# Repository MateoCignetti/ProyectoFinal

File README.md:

## Repositorio para el proyecto final de la carrera Ingeniería Electrónica. UTN FR San Francisco, 2025.

# Autores
- [ ] Alesandria, Alejo
- [ ] Cignetti, Mateo Antonio
- [ ] Galliano, Ignacio

Shield: [![CC BY-NC-SA 4.0][cc-by-nc-sa-shield]][cc-by-nc-sa]

Esta obra está bajo una
[Licencia Creative Commons Atribución-NoComercial-CompartirIgual 4.0 Internacional][cc-by-nc-sa].

[![CC BY-NC-SA 4.0][cc-by-nc-sa-image]][cc-by-nc-sa]

[cc-by-nc-sa]: https://creativecommons.org/licenses/by-nc-sa/4.0/deed.es
[cc-by-nc-sa-image]: https://licensebuttons.net/l/by-nc-sa/4.0/88x31.png
[cc-by-nc-sa-shield]: https://img.shields.io/badge/License-CC%20BY--NC--SA%204.0-lightgrey.svg

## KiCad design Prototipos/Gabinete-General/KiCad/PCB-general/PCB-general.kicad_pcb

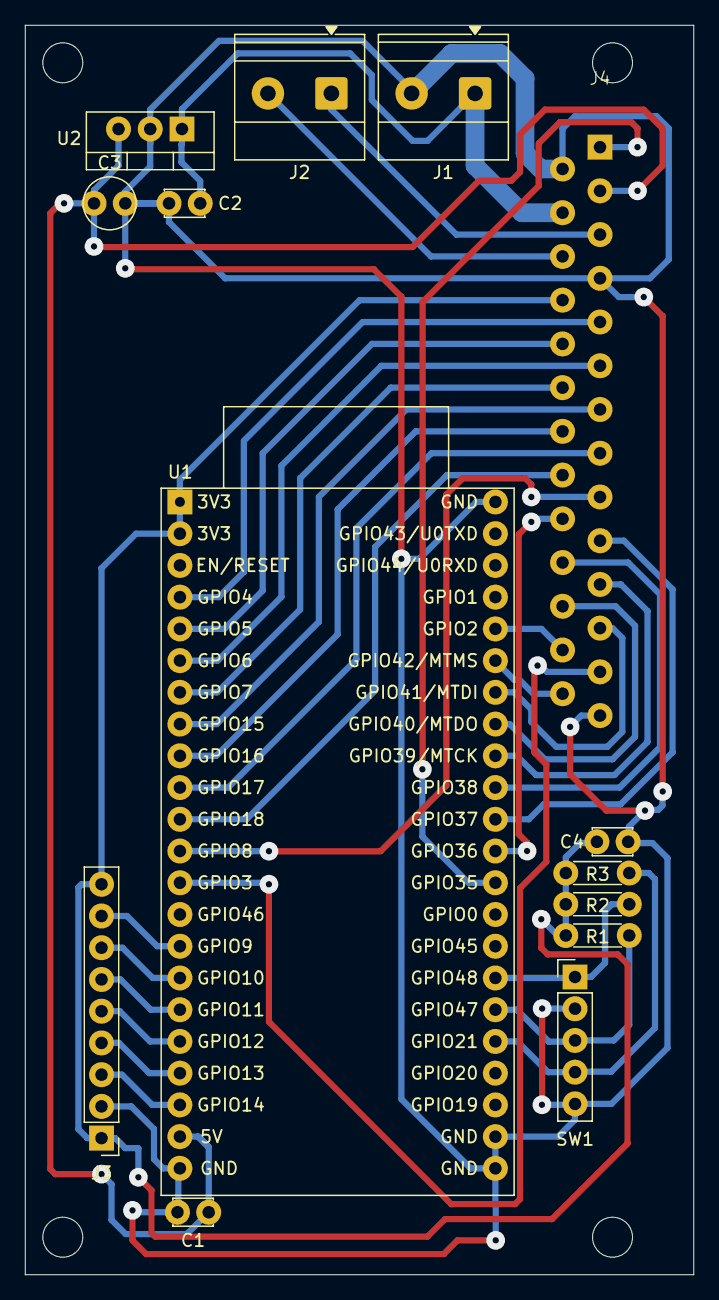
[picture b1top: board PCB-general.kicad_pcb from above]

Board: 2 copper layers, 53.5 x 100.0 mm, 18 parts (0 on the bottom side), 34 nets.

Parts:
C1, C2: 330 nF; C_Disc_D3.0mm_W2.0mm_P2.50mm
C3: 1uF; C_Radial_D4.0mm_H7.0mm_P1.50mm
C4: 100 nF; C_Disc_D3.0mm_W2.0mm_P2.50mm
J1, J2: Conn_01x02; TerminalBlock_Phoenix_MKDS-1,5-2-5.08_1x02_P5.08mm_Horizont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
J3: TFT Display; PinHeader_1x09_P2.54mm_Vertical
J4: PCIe X4; PCIE_x4_Gabinete_NSH
M3_BL, M3_BR, M3_TL, M3_TR: MountingHole_3.2mm_M3
R1, R2, R3: 10k; R_Axial_DIN0204_L3.6mm_D1.6mm_P5.08mm_Horizontal
SW1: RotaryEncoder_Switch; PinHeader_1x05_P2.54mm_Vertical
U1: ESP32-S3-DevKitC; ESP32-S3-DevKitC_NSH
U2: LM7805_TO220; TO-220-3_Vertical

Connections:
3.3Vdc: C4.2, J3.1 (Vcc), J3.9 (LED), J4.8 (3,3Vdc_Signal), R1.1, R2.1, R3.1, U1.1 (3V3), U1.2 (3V3)
5Vdc: C1.1, C3.1, J4.3 (5Vdc), U1.21 (5V), U2.3 (VO)
12Vdc: C2.1, J1.1, J4.4 (12Vdc), U2.1 (VI)
48Vac_L: J2.1, J4.5 (48Vac_L)
48Vac_N: J2.2, J4.6 (48Vac_N)
GND: C1.2, C2.2, C3.2, C4.1, J1.2, J3.2 (GND), J4.2 (PGND), J4.7 (AGND), SW1.2, SW1.5, U1.22 (GND), U1.23 (GND), U1.24 (GND), U1.44 (GND), U2.2 (GND)
PCIe_HP_Power: J4.1 (HP_Power), U1.32 (GPIO35)
PCIe_HP_Signal: J4.26 (HP_Signal), U1.39 (GPIO42/MTMS)
PCIe_MODULE_IDENT: J4.25 (MODULE_IDENT), U1.13 (GPIO3/ADC1_CH2)
PCIe_S1: J4.9 (S1), U1.4 (GPIO4/ADC1_CH3)
PCIe_S2: J4.10 (S2), U1.5 (GPIO5/ADC1_CH4)
PCIe_S3: J4.11 (S3), U1.6 (GPIO6/ADC1_CH5)
PCIe_S4: J4.12 (S4), U1.7 (GPIO7/ADC1_CH6)
PCIe_S5: J4.13 (S5), U1.8 (GPIO15/ADC2_CH4/32K_P)
PCIe_S6: J4.14 (S6), U1.9 (GPIO16/ADC2_CH5/32K_N)
PCIe_S7: J4.15 (S7), U1.10 (GPIO17/ADC2_CH6)
PCIe_S8: J4.16 (S8), U1.11 (GPIO18/ADC2_CH7)
PCIe_S9: J4.17 (S9), U1.12 (GPIO8/ADC1_CH7)
PCIe_S10: J4.18 (S10), U1.33 (GPIO36)
PCIe_S11: J4.19 (S11), U1.34 (GPIO37)
PCIe_S12: J4.20 (S12), U1.35 (GPIO38)
PCIe_S13: J4.21 (S13), U1.36 (GPIO39/MTCK)
PCIe_S14: J4.22 (S14), U1.37 (GPIO40/MTDO)
PCIe_S15: J4.23 (S15), U1.38 (GPIO41/MTDI)
PCIe_S16: J4.24 (S16), U1.40 (GPIO2/ADC1_CH1)
ROTARY_CLK: R2.2, SW1.1, U1.29 (GPIO48)
ROTARY_DATA: R1.2, SW1.3, U1.28 (GPIO47)
ROTARY_SW: R3.2, SW1.4, U1.27 (GPIO21)
TFT_CS: J3.3 (CS), U1.20 (GPIO14/ADC2_CH3)
TFT_DC: J3.5 (DC), U1.18 (GPIO12/ADC2_CH1)
TFT_MISO: J3.8 (MISO), U1.15 (GPIO9/ADC1_CH8)
TFT_MOSI: J3.6 (MOSI), U1.17 (GPIO11/ADC2_CH0)
TFT_RESET: J3.4 (RESET), U1.19 (GPIO13/ADC2_CH2)
TFT_SCK: J3.7 (SCK), U1.16 (GPIO10/ADC1_CH9)

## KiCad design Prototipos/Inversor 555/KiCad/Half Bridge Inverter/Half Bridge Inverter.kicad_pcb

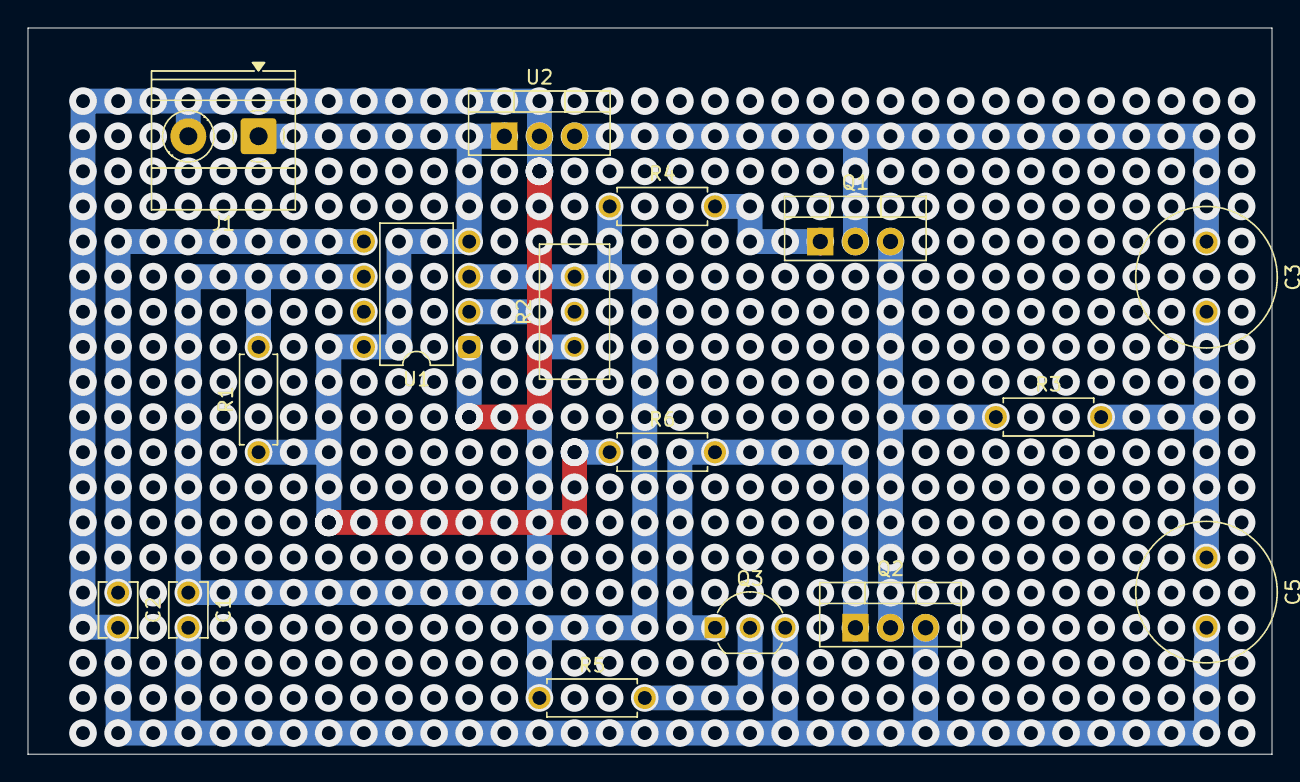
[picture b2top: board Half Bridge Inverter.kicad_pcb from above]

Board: 2 copper layers, 90.0 x 52.5 mm, 16 parts (0 on the bottom side), 11 nets.

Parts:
C1: 10u; C_Disc_D3.8mm_W2.6mm_P2.50mm
C2: 0.01u; C_Disc_D3.8mm_W2.6mm_P2.50mm
C3, C5: 1000u; C_Radial_D10.0mm_H16.0mm_P5.00mm
J1: Screw_Terminal_01x02; TerminalBlock_Phoenix_MKDS-1,5-2-5.08_1x02_P5.08mm_Horizont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
Q1, Q2: IRF4905; TO-220-3_Vertical
Q3: BC548; TO-92_Inline_Wide
R1: 100k; R_Axial_DIN0207_L6.3mm_D2.5mm_P7.62mm_Horizontal
R2: 1443; Potentiometer_Bourns_3296W_Vertical
R3: Carga; R_Axial_DIN0207_L6.3mm_D2.5mm_P7.62mm_Horizontal
R4: 100; R_Axial_DIN0207_L6.3mm_D2.5mm_P7.62mm_Horizontal
R5: 5,6k; R_Axial_DIN0207_L6.3mm_D2.5mm_P7.62mm_Horizontal
R6: 120; R_Axial_DIN0207_L6.3mm_D2.5mm_P7.62mm_Horizontal
U1: TLC555xD; DIP-8_W7.62mm
U2: LM7809_TO220; TO-220-3_Vertical

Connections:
555: R2.1, R4.1, R5.1, U1.3 (Q)
Earth: C1.2, C2.2, C5.2, J1.1, Q2.3 (S), Q3.3 (E), U1.1 (GND), U2.2 (GND)
unnamed: C3.2, C5.1, R3.2
unnamed: C3.1, Q1.2 (D), U2.3 (VO)
unnamed: Q1.1 (G), R4.2
unnamed: Q1.3 (S), Q2.2 (D), R3.1
unnamed: Q2.1 (G), Q3.1 (C), R6.2
unnamed: Q3.2 (B), R5.2
unnamed: C2.1, U1.5 (CV)
unnamed: C1.1, R1.2, R2.3, U1.2 (TR), U1.6 (THR)
VDD: J1.2, R1.1, R6.1, U1.4 (R), U1.8 (VCC), U2.1 (VI)

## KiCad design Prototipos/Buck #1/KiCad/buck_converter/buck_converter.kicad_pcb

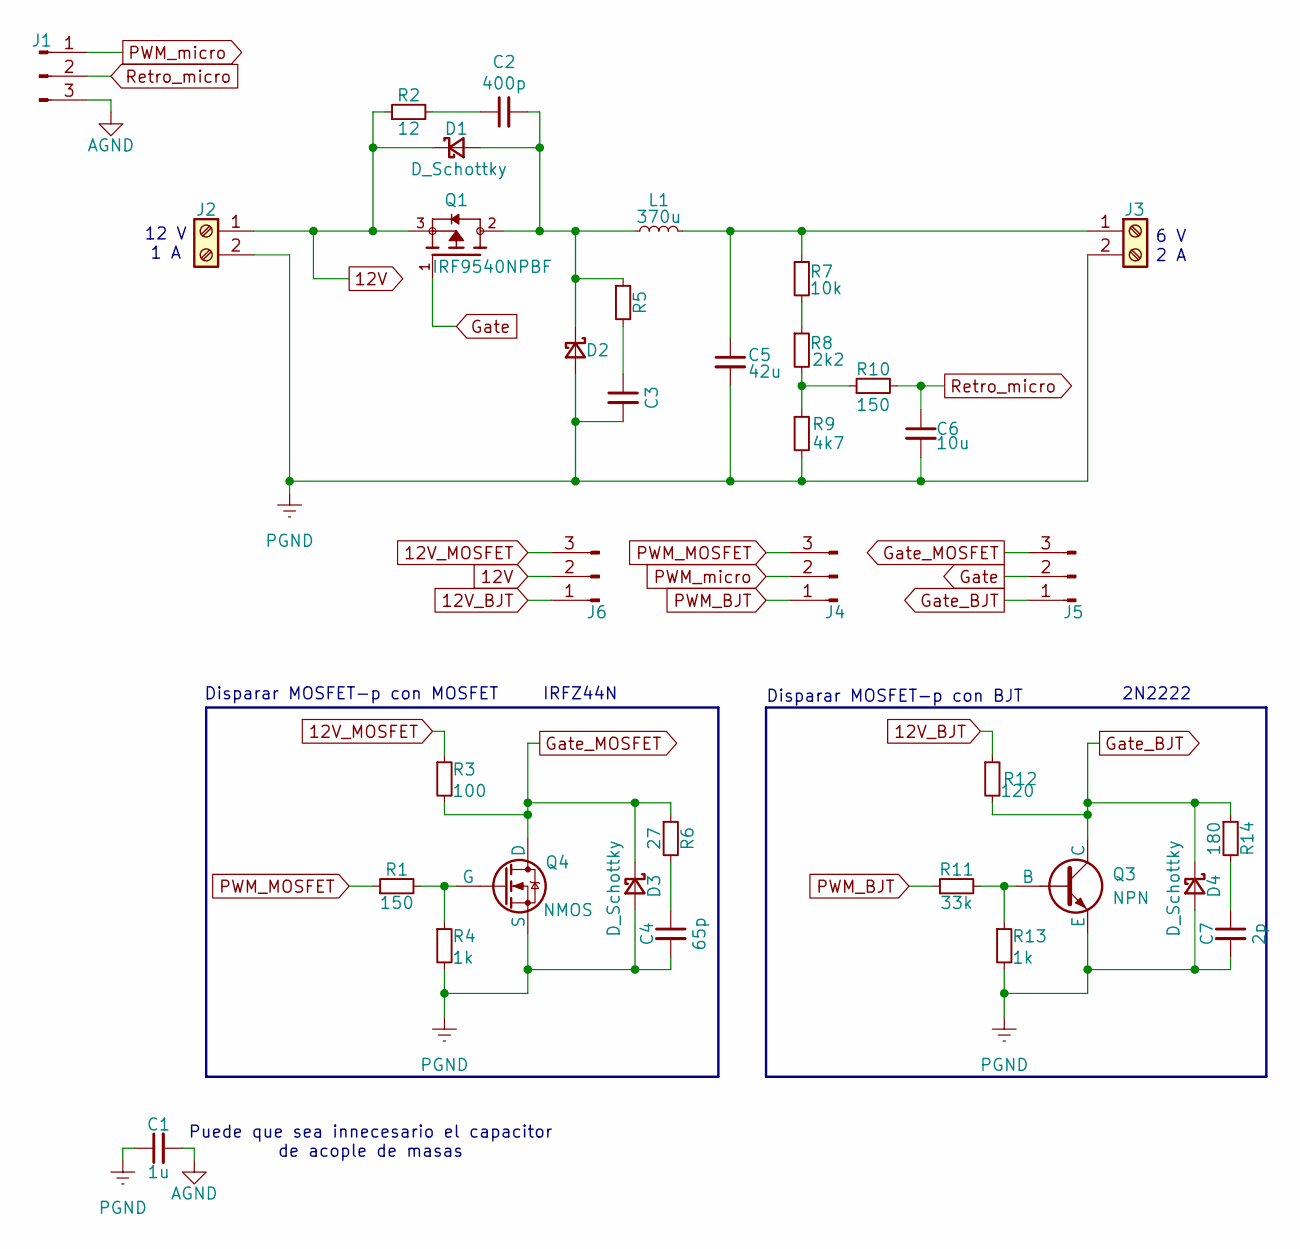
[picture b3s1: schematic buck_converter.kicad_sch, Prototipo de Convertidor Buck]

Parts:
C1: 1u; C_Disc_D3.8mm_W2.6mm_P2.50mm
C2: 400p; C_Disc_D3.8mm_W2.6mm_P2.50mm
C3: C_Disc_D3.8mm_W2.6mm_P2.50mm
C4: 65p; C_Disc_D3.8mm_W2.6mm_P2.50mm
C5: 42u; C_Disc_D3.8mm_W2.6mm_P2.50mm
C6: 10u; C_Disc_D3.8mm_W2.6mm_P2.50mm
C7: 2p; C_Disc_D3.8mm_W2.6mm_P2.50mm
D1, D2, D3, D4: D_Schottky; D_DO-34_SOD68_P7.62mm_Horizontal
J1, J4, J5, J6: Conn_01x03_Pin; PinHeader_1x03_P2.54mm_Vertical
J2, J3: Screw_Terminal_01x02; TerminalBlock_Phoenix_MKDS-1,5-2-5.08_1x02_P5.08mm_Horizont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
L1: 370u; L_Axial_L16.0mm_D6.3mm_P25.40mm_Horizontal_Fastron_VHBCC
Q1: IRF9540NPBF; TO254P470X1000X2000-3P; PARTREV B
Q3: NPN; TO-92_Inline_Wide
Q4: NMOS; TO-220-3_Vertical
R1, R10: 150; R_Axial_DIN0207_L6.3mm_D2.5mm_P7.62mm_Horizontal
R2: 12; R_Axial_DIN0207_L6.3mm_D2.5mm_P7.62mm_Horizontal
R3: 100; R_Axial_DIN0207_L6.3mm_D2.5mm_P7.62mm_Horizontal
R4, R13: 1k; R_Axial_DIN0207_L6.3mm_D2.5mm_P7.62mm_Horizontal
R5: R_Axial_DIN0207_L6.3mm_D2.5mm_P7.62mm_Horizontal
R6: 27; R_Axial_DIN0207_L6.3mm_D2.5mm_P7.62mm_Horizontal
R7: 10k; R_Axial_DIN0207_L6.3mm_D2.5mm_P7.62mm_Horizontal
R8: 2k2; R_Axial_DIN0207_L6.3mm_D2.5mm_P7.62mm_Horizontal
R9: 4k7; R_Axial_DIN0207_L6.3mm_D2.5mm_P7.62mm_Horizontal
R11: 33k; R_Axial_DIN0207_L6.3mm_D2.5mm_P7.62mm_Horizontal
R12: 120; R_Axial_DIN0207_L6.3mm_D2.5mm_P7.62mm_Horizontal
R14: 180; R_Axial_DIN0207_L6.3mm_D2.5mm_P7.62mm_Horizontal

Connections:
12V: D1.1 (K), J2.1, J6.2, Q1.3, R2.1
12V_BJT: J6.1, R12.1
12V_MOSFET: J6.3, R3.1
AGND: C1.2, J1.3
Gate: J5.2, Q1.1
Gate_BJT: D4.1 (K), J5.1, Q3.3 (C), R12.2, R14.1
Gate_MOSFET: D3.1 (K), J5.3, Q4.2 (D), R3.2, R6.1
unnamed: C2.1, R2.2
unnamed: C3.1, R5.2
unnamed: C4.1, R6.2
unnamed: C7.1, R14.2
unnamed: C2.2, D1.2 (A), D2.1 (K), L1.1, Q1.2, R5.1
unnamed: C5.1, J3.1, L1.2, R7.1
unnamed: Q3.2 (B), R11.2, R13.1
unnamed: Q4.1 (G), R1.2, R4.1
unnamed: R7.2, R8.1
unnamed: R8.2, R9.1, R10.1
PGND: C1.1, C3.2, C4.2, C5.2, C6.2, C7.2, D2.2 (A), D3.2 (A), D4.2 (A), J2.2, J3.2, Q3.1 (E), Q4.3 (S), R4.2, R9.2, R13.2
PWM_BJT: J4.1, R11.1
PWM_MOSFET: J4.3, R1.1
PWM_micro: J1.1, J4.2
Retro_micro: C6.1, J1.2, R10.2

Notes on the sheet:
Puede que sea innecesario el capacitor de acople de masas
2N2222
IRFZ44N
6 V 2 A
Disparar MOSFET-p con BJT
12 V 1 A
Disparar MOSFET-p con MOSFET

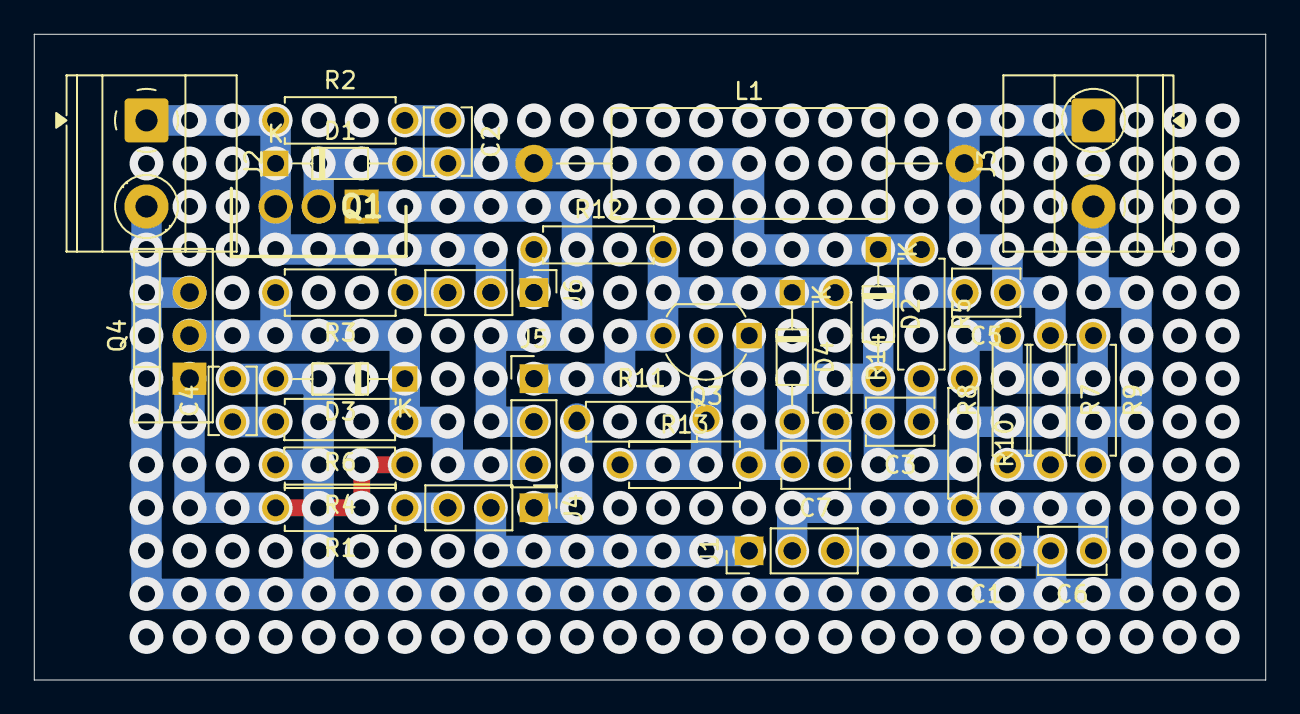
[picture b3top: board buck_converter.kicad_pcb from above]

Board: 2 copper layers, 72.7 x 38.1 mm, 35 parts (0 on the bottom side), 22 nets.

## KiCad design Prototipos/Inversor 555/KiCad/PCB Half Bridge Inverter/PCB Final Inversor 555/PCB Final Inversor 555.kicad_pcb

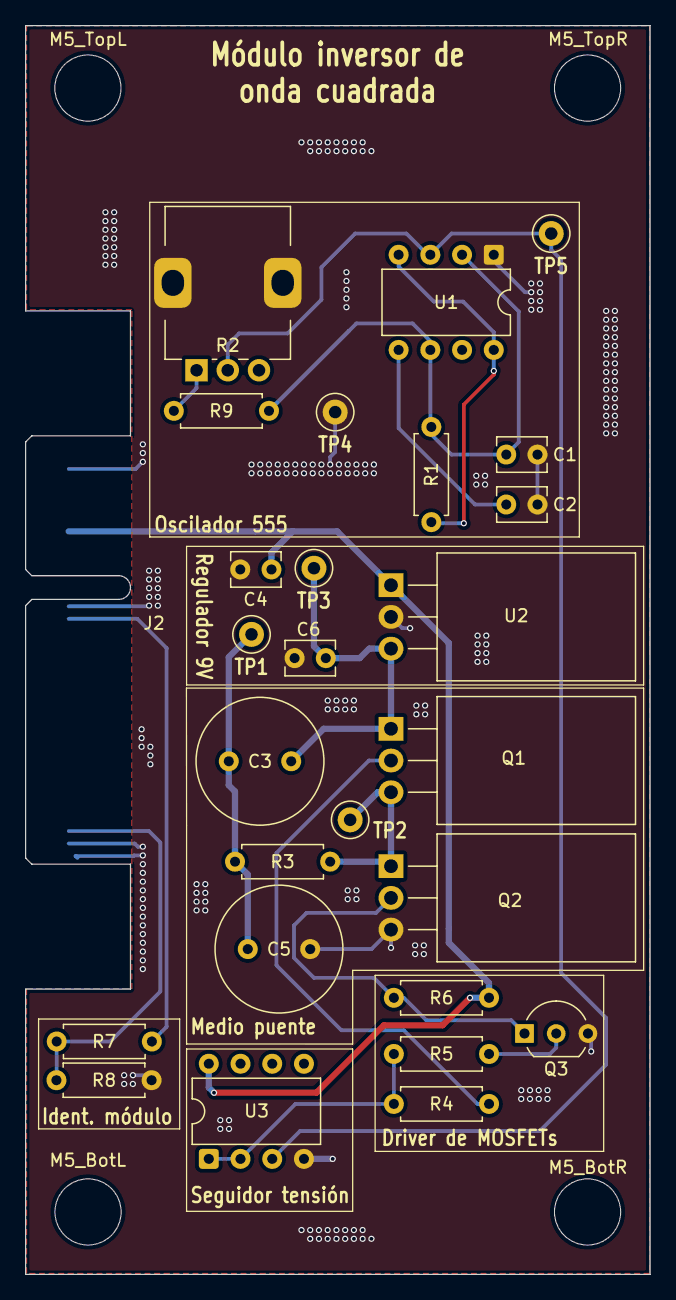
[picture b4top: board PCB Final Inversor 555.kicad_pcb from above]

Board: 2 copper layers, 50.0 x 100.0 mm, 31 parts (0 on the bottom side), 15 nets.

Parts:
C1, C6: 0.1u; C_Disc_D3.8mm_W2.6mm_P2.50mm
C2: 0.01u; C_Disc_D3.8mm_W2.6mm_P2.50mm
C3, C5: 1500u; C_Radial_D10.0mm_H16.0mm_P5.00mm
C4: 0.33u; C_Disc_D3.8mm_W2.6mm_P2.50mm
J2: BUS_PCIE_x4_NSH
M5_BotL, M5_BotR, M5_TopL, M5_TopR: MountingHole_5.3mm_M5
Q1, Q2: IRFZ44; TO-220-3_Horizontal_TabDown
Q3: BC548; TO-92_Inline_Wide
R1: 10M; R_Axial_DIN0207_L6.3mm_D2.5mm_P7.62mm_Horizontal
R2: 50k; Potentiometer_Alps_RK09K_Single_Vertical
R3: Load; R_Axial_DIN0207_L6.3mm_D2.5mm_P7.62mm_Horizontal
R4, R6: 1.2k; R_Axial_DIN0207_L6.3mm_D2.5mm_P7.62mm_Horizontal
R5: 330k; R_Axial_DIN0207_L6.3mm_D2.5mm_P7.62mm_Horizontal
R7, R8: 10k; R_Axial_DIN0207_L6.3mm_D2.5mm_P7.62mm_Horizontal
R9: 120k; R_Axial_DIN0207_L6.3mm_D2.5mm_P7.62mm_Horizontal
TP1: Load-; TestPoint_Loop_D1.80mm_Drill1.0mm_Beaded
TP2: Load+; TestPoint_Loop_D1.80mm_Drill1.0mm_Beaded
TP3: Regulator_output; TestPoint_Loop_D1.80mm_Drill1.0mm_Beaded
TP4: GND; TestPoint_Loop_D1.80mm_Drill1.0mm_Beaded
TP5: 555_OUT; TestPoint_Loop_D1.80mm_Drill1.0mm_Beaded
U1: TLC555xD; DIP-8_W7.62mm
U2: LM7809_TO220; TO-220-3_Horizontal_TabDown
U3: LM358; DIP-8_W7.62mm

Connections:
3,3Vdc: J2.8 (3,3Vdc_Signal), R7.1
9Vdc: C3.1, C6.1, Q1.1 (D), TP3.1, U2.3 (VO)
12Vdc: C4.1, J2.4 (12Vdc), R1.2, R6.1, U1.4 (R), U1.8 (VCC), U2.1 (VI), U3.8 (V+)
555: R2.2, TP5.1, U1.3 (Q), U3.3 (+)
GND: C1.2, C2.2, C4.2, C5.2, C6.2, J2.1 (HP_Power), J2.2 (PGND), J2.7 (AGND), J2.26 (HP_Signal), Q2.3 (S), Q3.3 (E), R2.MP, R8.2, TP4.1, U1.1 (GND), U2.2 (GND), U3.4 (V-)
Module_ident: J2.25 (MODULE_IDENT), R7.2, R8.1
unnamed: C3.2, C5.1, R3.2, TP1.1
unnamed: Q1.2 (G), R4.2
unnamed: Q1.3 (S), Q2.1 (D), R3.1, TP2.1
unnamed: Q2.2 (G), Q3.1 (C), R6.2
unnamed: Q3.2 (B), R5.2
unnamed: R2.1, R9.2
unnamed: C2.1, U1.5 (CV)
unnamed: C1.1, R1.1, R9.1, U1.2 (TR), U1.6 (THR)
VF_Out: R4.1, R5.1, U3.1, U3.2 (-)

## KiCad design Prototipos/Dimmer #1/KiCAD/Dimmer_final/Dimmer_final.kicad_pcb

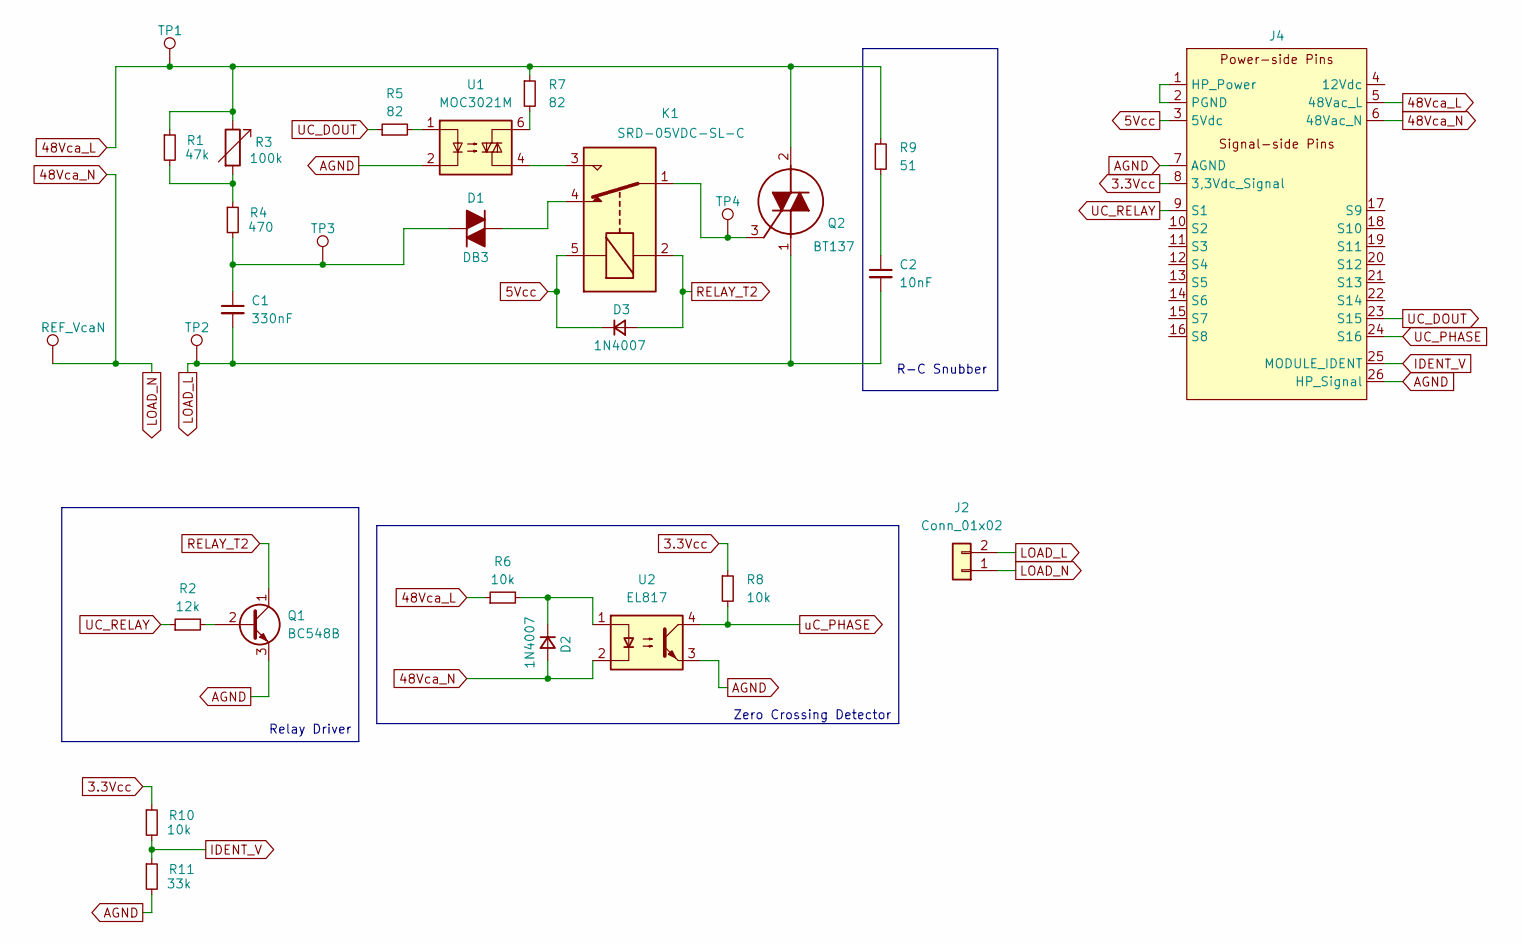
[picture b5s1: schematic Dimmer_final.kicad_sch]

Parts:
C1: 330nF; C_Disc_D4.7mm_W2.5mm_P5.00mm
C2: 10nF; C_Disc_D4.7mm_W2.5mm_P5.00mm
D1: DB3; D_DO-35_SOD27_P7.62mm_Horizontal
D2, D3: 1N4007; D_DO-41_SOD81_P7.62mm_Horizontal
J2: Conn_01x02; TerminalBlock_Phoenix_MKDS-1,5-2-5.08_1x02_P5.08mm_Horizont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
J4: BUS_PCIE_x4_NSH
K1: SRD-05VDC-SL-C; Relay_SPDT_SANYOU_SRD_Series_Form_C
Q1: BC548B; TO-92_Inline_Wide
Q2: BT137; TO-220-3_Horizontal_TabDown; Mouser Part Number 771-BT137-600E
R1: 47k; R_Axial_DIN0207_L6.3mm_D2.5mm_P7.62mm_Horizontal
R2: 12k; R_Axial_DIN0207_L6.3mm_D2.5mm_P7.62mm_Horizontal
R3: 100k; Potentiometer_Alps_RK09K_Single_Vertical
R4: 470; R_Axial_DIN0207_L6.3mm_D2.5mm_P7.62mm_Horizontal
R5, R7: 82; R_Axial_DIN0207_L6.3mm_D2.5mm_P7.62mm_Horizontal
R6, R8, R10: 10k; R_Axial_DIN0207_L6.3mm_D2.5mm_P7.62mm_Horizontal
R9: 51; R_Axial_DIN0207_L6.3mm_D2.5mm_P7.62mm_Horizontal
R11: 33k; R_Axial_DIN0207_L6.3mm_D2.5mm_P7.62mm_Horizontal
REF_VcaN: TestPoint; TestPoint_Loop_D1.80mm_Drill1.0mm_Beaded
TP1, TP2, TP3, TP4: TestPoint; TestPoint_Loop_D1.80mm_Drill1.0mm_Beaded
U1: MOC3021M; DIP762W45P254L889H508Q6
U2: EL817; DIP-4_W7.62mm

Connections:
3.3Vcc: J4.8 (3,3Vdc_Signal), R8.1, R10.1
5Vcc: D3.1 (K), J4.3 (5Vdc), K1.5
48Vca_L: J4.5 (48Vac_L), Q2.2 (MT2), R1.1, R3.1, R3.3, R6.1, R7.1, R9.1, TP1.1
48Vca_N: D2.2 (A), J2.1, J4.6 (48Vac_N), REF_VcaN.1, U2.2; also elsewhere on the board
AGND: J4.7 (AGND), J4.26 (HP_Signal), Q1.3 (E), R11.2, U1.2, U2.3
IDENT_V: J4.25 (MODULE_IDENT), R10.2, R11.1
LOAD_L: C1.2, C2.2, J2.2, Q2.1 (MT1), TP2.1
unnamed: C2.1, R9.2
unnamed: D1.2 (A), K1.4
unnamed: C1.1, D1.1 (K), R4.2, TP3.1
unnamed: D2.1 (K), R6.2, U2.1
unnamed: J4.1 (HP_Power), J4.2 (PGND)
unnamed: K1.3, U1.4
unnamed: Q1.2 (B), R2.2
unnamed: K1.1, Q2.3 (G), TP4.1
unnamed: R1.2, R3.2, R4.1
unnamed: R5.2, U1.1
unnamed: R7.2, U1.6
RELAY_T2: D3.2 (A), K1.2, Q1.1 (C)
uC_DOUT: J4.23 (S15), R5.1
uC_PHASE: J4.24 (S16), R8.2, U2.4
uC_RELAY: J4.9 (S1), R2.1

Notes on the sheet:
R-C Snubber
Zero Crossing Detector
Relay Driver

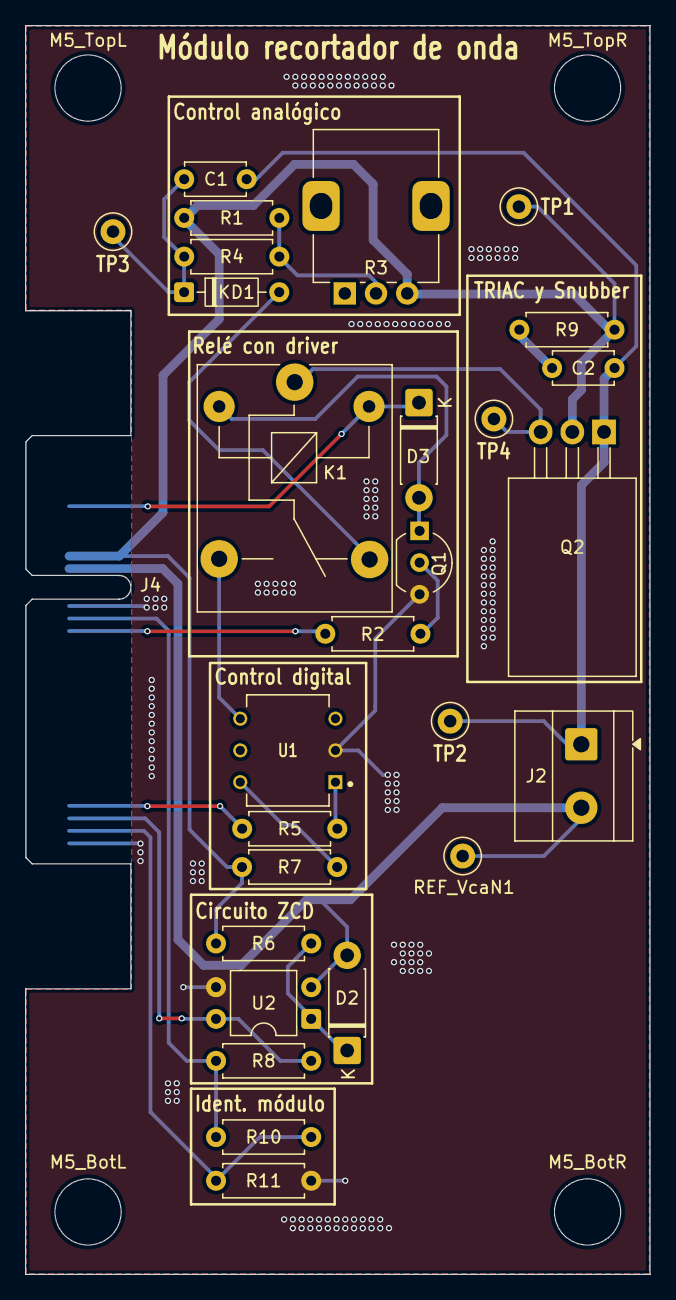
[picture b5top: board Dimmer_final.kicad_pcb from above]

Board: 2 copper layers, 50.0 x 100.0 mm, 32 parts (0 on the bottom side), 22 nets.

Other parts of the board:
M5_BotL, M5_BotR, M5_TopL, M5_TopR: MountingHole_5.3mm_M5
REF_VcaN1: TestPoint; TestPoint_Loop_D1.80mm_Drill1.0mm_Beaded

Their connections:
48Vca_N: REF_VcaN1.1; also elsewhere on the board

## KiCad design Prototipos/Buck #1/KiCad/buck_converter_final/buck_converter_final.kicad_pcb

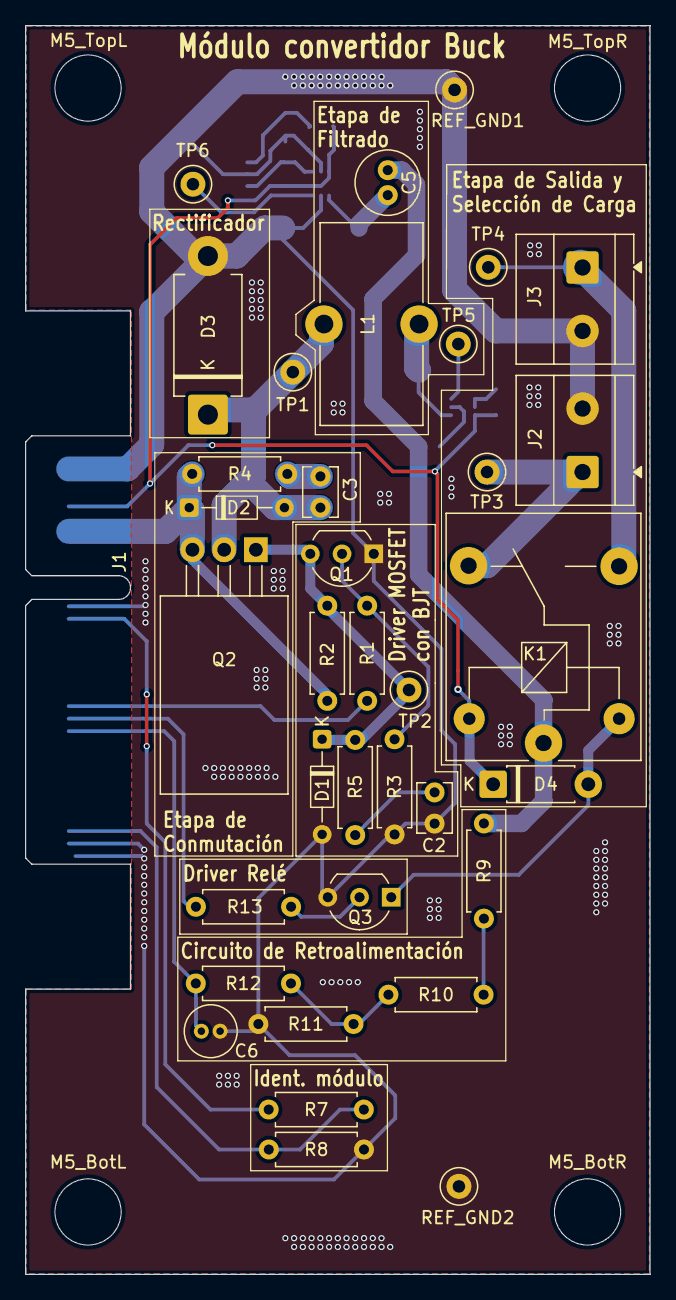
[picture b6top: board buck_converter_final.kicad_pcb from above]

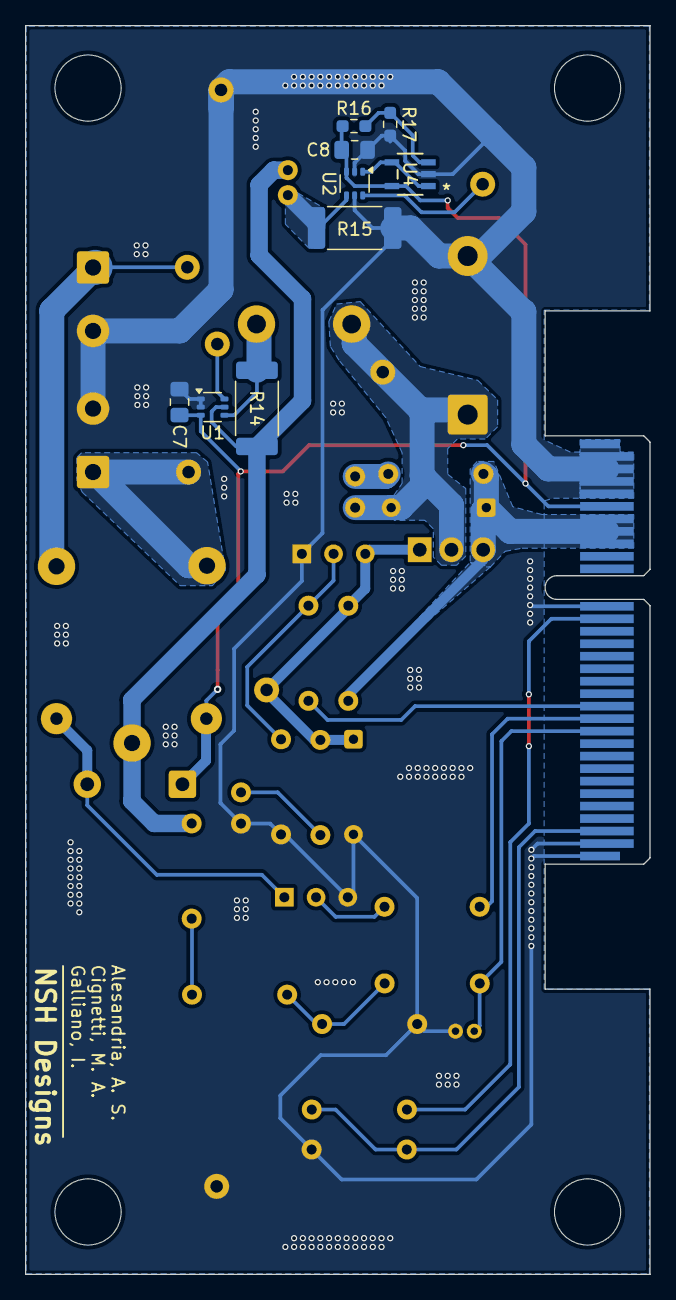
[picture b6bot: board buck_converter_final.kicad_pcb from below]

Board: 2 copper layers, 50.0 x 100.0 mm, 49 parts (9 on the bottom side), 26 nets.

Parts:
C2: 2p; C_Disc_D3.8mm_W2.6mm_P2.50mm
C3: 400p; C_Disc_D3.8mm_W2.6mm_P2.50mm
C5: 47u; C_Radial_D5.0mm_H11.0mm_P2.00mm
C6: 10u; C_Radial_D4.0mm_H7.0mm_P1.50mm
C7, C8: 0.1uF; C_0805_2012Metric_Pad1.18x1.45mm_HandSolder
D1, D2: 1N5819; D_DO-34_SOD68_P7.62mm_Horizontal
D3: SR560; D_DO-201AD_P12.70mm_Horizontal
D4: 1N4007; D_DO-41_SOD81_P7.62mm_Horizontal
J1: BUS_PCIE_x4_NSH
J2, J3: Screw_Terminal_01x02; TerminalBlock_Phoenix_MKDS-1,5-2-5.08_1x02_P5.08mm_Horizont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
K1: SANYOU_SRD_Form_C; Relay_SPDT_SANYOU_SRD_Series_Form_C
L1: 370u; L_Toroid_Vertical_L16.0mm_W8.0mm_P7.62mm
M5_BotL, M5_BotR, M5_TopL, M5_TopR: MountingHole_5.3mm_M5
Q1: NPN; TO-92_Inline_Wide
Q2: IRF9540NPBF; TO-220-3_Horizontal_TabDown
Q3: BC548; TO-92_Inline_Wide
R1, R10: 2.2k; R_Axial_DIN0207_L6.3mm_D2.5mm_P7.62mm_Horizontal
R2: 120; R_Axial_DIN0207_L6.3mm_D2.5mm_P7.62mm_Horizontal
R3: 100k; R_Axial_DIN0207_L6.3mm_D2.5mm_P7.62mm_Horizontal
R4: 12; R_Axial_DIN0207_L6.3mm_D2.5mm_P7.62mm_Horizontal
R5: 180; R_Axial_DIN0207_L6.3mm_D2.5mm_P7.62mm_Horizontal
R7, R9: 10k; R_Axial_DIN0207_L6.3mm_D2.5mm_P7.62mm_Horizontal
R8: 15k; R_Axial_DIN0207_L6.3mm_D2.5mm_P7.62mm_Horizontal
R11: 4.7k; R_Axial_DIN0207_L6.3mm_D2.5mm_P7.62mm_Horizontal
R12: 150; R_Axial_DIN0207_L6.3mm_D2.5mm_P7.62mm_Horizontal
R13: 12k; R_Axial_DIN0207_L6.3mm_D2.5mm_P7.62mm_Horizontal
R14: 10m; R_2512_6332Metric_Pad1.40x3.35mm_HandSolder
R15: 5m; R_2512_6332Metric_Pad1.40x3.35mm_HandSolder
R16, R17: 4.7k; R_0603_1608Metric_Pad0.98x0.95mm_HandSolder
REF_GND1, REF_GND2: GND; TestPoint_Loop_D1.80mm_Drill1.0mm_Beaded
TP1: DRAIN; TestPoint_Loop_D1.80mm_Drill1.0mm_Beaded
TP2: GATE; TestPoint_Loop_D1.80mm_Drill1.0mm_Beaded
TP3: LOAD_1; TestPoint_Loop_D1.80mm_Drill1.0mm_Beaded
TP4: LOAD_2; TestPoint_Loop_D1.80mm_Drill1.0mm_Beaded
TP5: INDUCTOR_CURRENT; TestPoint_Loop_D1.80mm_Drill1.0mm_Beaded
TP6: CAPACITOR_CURRENT; TestPoint_Loop_D1.80mm_Drill1.0mm_Beaded
U1, U2: INA199xxDCK; SOT-363_SC-70-6
U4: TL071HIDBVR; SOT23_DBV_5_TEX-M

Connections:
3.3Vcc: J1.8 (3,3Vdc_Signal), R7.1
5Vdc: C7.1, C8.1, D4.1 (K), J1.3 (5Vdc), K1.5, R16.1, U1.3 (V+), U2.3 (V+), U4.5 (V+)
12V: D2.1 (K), J1.4 (12Vdc), Q2.3, R2.1, R4.1
C_CURRENT_+: C5.2, R15.2, U2.4 (+)
GATE: D1.1 (K), Q1.3 (C), Q2.1, R2.2, R5.1, TP2.1
GND: C2.2, C6.2, C7.2, C8.2, D1.2 (A), D3.2 (A), J1.1 (HP_Power), J1.2 (PGND), J1.7 (AGND), J1.26 (HP_Signal), J2.2, J3.2, Q1.1 (E), Q3.3 (E), R3.2, R8.2, R11.2, R15.1, R17.1, REF_GND1.1, REF_GND2.1, U1.1 (REF), U1.2 (GND), U2.2 (GND), U2.5 (-), U4.2 (V-)
IDENT_V: J1.25 (MODULE_IDENT), R7.2, R8.1
INDUCTIVE_LOAD: J3.1, K1.3, TP4.1
I_CURRENT_+: L1.2, R14.1, U1.4 (+)
I_CURRENT_-: C5.1, K1.1, R9.1, R14.2, U1.5 (-)
unnamed: C2.1, R5.2
unnamed: C3.1, R4.2
unnamed: C3.2, D2.2 (A), D3.1 (K), L1.1, Q2.2, TP1.1
unnamed: Q1.2 (B), R1.2, R3.1
unnamed: Q3.2 (B), R13.2
unnamed: R9.2, R10.1
unnamed: R10.2, R11.1, R12.1
unnamed: TP5.1, U1.6
unnamed: TP6.1, U2.6
unnamed: U2.1 (REF), U4.1, U4.4 (-)
unnamed: R16.2, R17.2, U4.3 (+)
PWM_CONTROL: J1.15 (S7), R1.1
RELAY_T2: D4.2 (A), K1.2, Q3.1 (C)
RESISTIVE_LOAD: J2.1, K1.4, TP3.1
RETRO_MICRO: C6.1, J1.17 (S9), R12.2
UC_RELAY: J1.16 (S8), R13.1

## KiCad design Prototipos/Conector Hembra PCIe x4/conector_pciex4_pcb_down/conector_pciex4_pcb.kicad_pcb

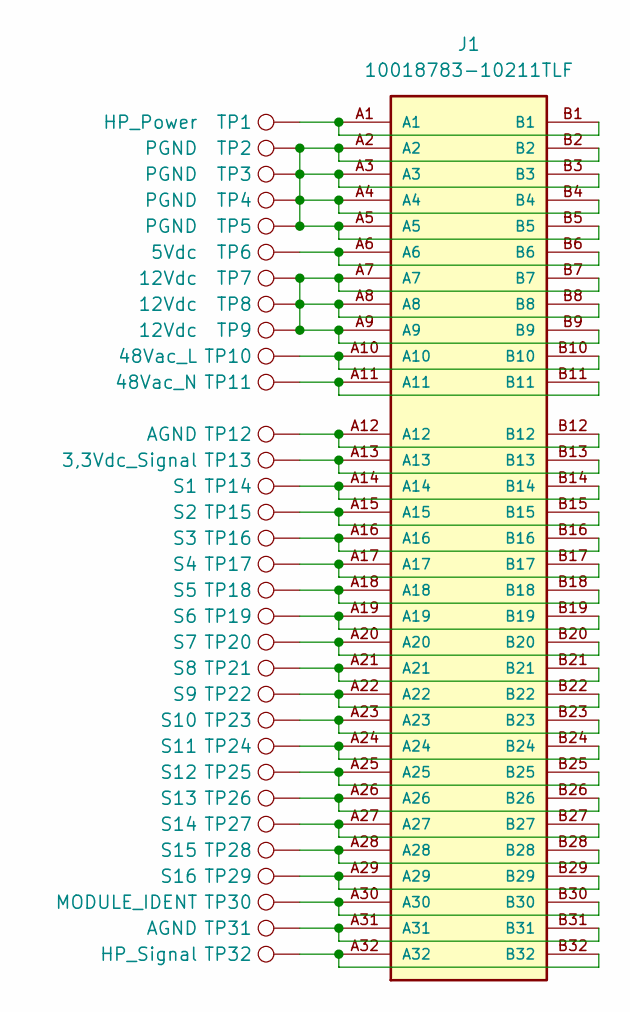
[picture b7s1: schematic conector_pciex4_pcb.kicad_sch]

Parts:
J1: 10018783-10211TLF; AMPHENOL_10018783-10211TLF; PARTREV AA
TP1: HP_Power; TestPoint_THTPad_D1.5mm_Drill0.7mm
TP2, TP3, TP4, TP5: PGND; TestPoint_THTPad_D1.5mm_Drill0.7mm
TP6: 5Vdc; TestPoint_THTPad_D1.5mm_Drill0.7mm
TP7, TP8, TP9: 12Vdc; TestPoint_THTPad_D1.5mm_Drill0.7mm
TP10: 48Vac_L; TestPoint_THTPad_D1.5mm_Drill0.7mm
TP11: 48Vac_N; TestPoint_THTPad_D1.5mm_Drill0.7mm
TP12, TP31: AGND; TestPoint_THTPad_D1.5mm_Drill0.7mm
TP13: 3,3Vdc_Signal; TestPoint_THTPad_D1.5mm_Drill0.7mm
TP14: S1; TestPoint_THTPad_D1.5mm_Drill0.7mm
TP15: S2; TestPoint_THTPad_D1.5mm_Drill0.7mm
TP16: S3; TestPoint_THTPad_D1.5mm_Drill0.7mm
TP17: S4; TestPoint_THTPad_D1.5mm_Drill0.7mm
TP18: S5; TestPoint_THTPad_D1.5mm_Drill0.7mm
TP19: S6; TestPoint_THTPad_D1.5mm_Drill0.7mm
TP20: S7; TestPoint_THTPad_D1.5mm_Drill0.7mm
TP21: S8; TestPoint_THTPad_D1.5mm_Drill0.7mm
TP22: S9; TestPoint_THTPad_D1.5mm_Drill0.7mm
TP23: S10; TestPoint_THTPad_D1.5mm_Drill0.7mm
TP24: S11; TestPoint_THTPad_D1.5mm_Drill0.7mm
TP25: S12; TestPoint_THTPad_D1.5mm_Drill0.7mm
TP26: S13; TestPoint_THTPad_D1.5mm_Drill0.7mm
TP27: S14; TestPoint_THTPad_D1.5mm_Drill0.7mm
TP28: S15; TestPoint_THTPad_D1.5mm_Drill0.7mm
TP29: S16; TestPoint_THTPad_D1.5mm_Drill0.7mm
TP30: MODULE_IDENT; TestPoint_THTPad_D1.5mm_Drill0.7mm
TP32: HP_Signal; TestPoint_THTPad_D1.5mm_Drill0.7mm

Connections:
unnamed: J1.A1, J1.B1, TP1.1
unnamed: J1.A2, J1.A3, J1.A4, J1.A5, J1.B2, J1.B3, J1.B4, J1.B5, TP2.1, TP3.1, TP4.1, TP5.1
unnamed: J1.A6, J1.B6, TP6.1
unnamed: J1.A7, J1.A8, J1.A9, J1.B7, J1.B8, J1.B9, TP7.1, TP8.1, TP9.1
unnamed: J1.A10, J1.B10, TP10.1
unnamed: J1.A11, J1.B11, TP11.1
unnamed: J1.A12, J1.B12, TP12.1
unnamed: J1.A13, J1.B13, TP13.1
unnamed: J1.A14, J1.B14, TP14.1
unnamed: J1.A15, J1.B15, TP15.1
unnamed: J1.A16, J1.B16, TP16.1
unnamed: J1.A17, J1.B17, TP17.1
unnamed: J1.A18, J1.B18, TP18.1
unnamed: J1.A19, J1.B19, TP19.1
unnamed: J1.A20, J1.B20, TP20.1
unnamed: J1.A21, J1.B21, TP21.1
unnamed: J1.A22, J1.B22, TP22.1
unnamed: J1.A23, J1.B23, TP23.1
unnamed: J1.A24, J1.B24, TP24.1
unnamed: J1.A25, J1.B25, TP25.1
unnamed: J1.A26, J1.B26, TP26.1
unnamed: J1.A27, J1.B27, TP27.1
unnamed: J1.A28, J1.B28, TP28.1
unnamed: J1.A29, J1.B29, TP29.1
unnamed: J1.A30, J1.B30, TP30.1
unnamed: J1.A31, J1.B31, TP31.1
unnamed: J1.A32, J1.B32, TP32.1

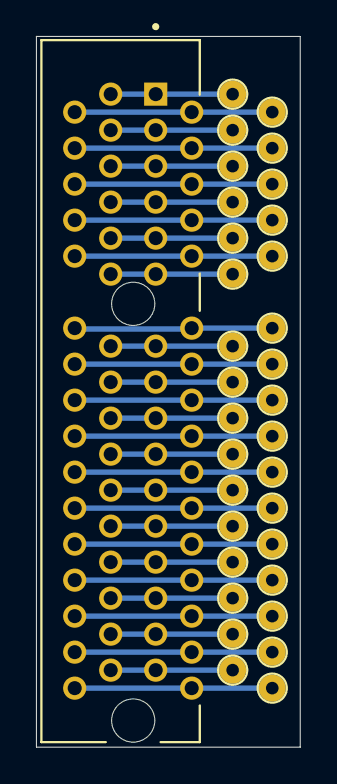
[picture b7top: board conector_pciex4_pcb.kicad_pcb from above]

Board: 2 copper layers, 14.7 x 39.5 mm, 33 parts (0 on the bottom side), 27 nets.

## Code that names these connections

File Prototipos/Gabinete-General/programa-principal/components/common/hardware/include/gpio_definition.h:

#ifndef GPIO_DEFINITION_H
#define GPIO_DEFINITION_H

#include "soc/gpio_num.h"
#include "hal/adc_types.h"

#define PIN_HP_POWER GPIO_NUM_35
#define PIN_HP_SIGNAL GPIO_NUM_42
#define PIN_MODULE_IDENT GPIO_NUM_3

#define ADC_MODULE_IDENT_UNIT ADC_UNIT_1
#define ADC_MODULE_IDENT_CHANNEL ADC_CHANNEL_2

#define PIN_S1 GPIO_NUM_4
#define PIN_S2 GPIO_NUM_5
#define PIN_S3 GPIO_NUM_6
#define PIN_S4 GPIO_NUM_7
#define PIN_S5 GPIO_NUM_15
#define PIN_S6 GPIO_NUM_16
#define PIN_S7 GPIO_NUM_17
#define PIN_S8 GPIO_NUM_18
#define PIN_S9 GPIO_NUM_8
#define PIN_S10 GPIO_NUM_36
#define PIN_S11 GPIO_NUM_37
#define PIN_S12 GPIO_NUM_38
#define PIN_S13 GPIO_NUM_39
#define PIN_S14 GPIO_NUM_40
#define PIN_S15 GPIO_NUM_41
#define PIN_S16 GPIO_NUM_2

#define ADC_S1_UNIT ADC_UNIT_1
#define ADC_S1_CHANNEL ADC_CHANNEL_3
#define ADC_S2_UNIT ADC_UNIT_1
#define ADC_S2_CHANNEL ADC_CHANNEL_4
#define ADC_S3_UNIT ADC_UNIT_1
#define ADC_S3_CHANNEL ADC_CHANNEL_5
#define ADC_S4_UNIT ADC_UNIT_1
#define ADC_S4_CHANNEL ADC_CHANNEL_6
#define ADC_S5_UNIT ADC_UNIT_2
#define ADC_S5_CHANNEL ADC_CHANNEL_4
#define ADC_S6_UNIT ADC_UNIT_2
#define ADC_S6_CHANNEL ADC_CHANNEL_5
#define ADC_S7_UNIT ADC_UNIT_2
#define ADC_S7_CHANNEL ADC_CHANNEL_6
#define ADC_S8_UNIT ADC_UNIT_2
#define ADC_S8_CHANNEL ADC_CHANNEL_7
#define ADC_S9_UNIT ADC_UNIT_1
#define ADC_S9_CHANNEL ADC_CHANNEL_7
#define ADC_S16_UNIT ADC_UNIT_1
#define ADC_S16_CHANNEL ADC_CHANNEL_1

#define PIN_ROTARY_DATA GPIO_NUM_47
#define PIN_ROTARY_CLK GPIO_NUM_48
#define PIN_ROTARY_SW GPIO_NUM_21

#define PIN_TFT_MISO GPIO_NUM_9
#define PIN_TFT_SCK GPIO_NUM_10
#define PIN_TFT_MOSI GPIO_NUM_11
#define PIN_TFT_DC GPIO_NUM_12
#define PIN_TFT_RESET GPIO_NUM_13
#define PIN_TFT_CS GPIO_NUM_14

#endif
